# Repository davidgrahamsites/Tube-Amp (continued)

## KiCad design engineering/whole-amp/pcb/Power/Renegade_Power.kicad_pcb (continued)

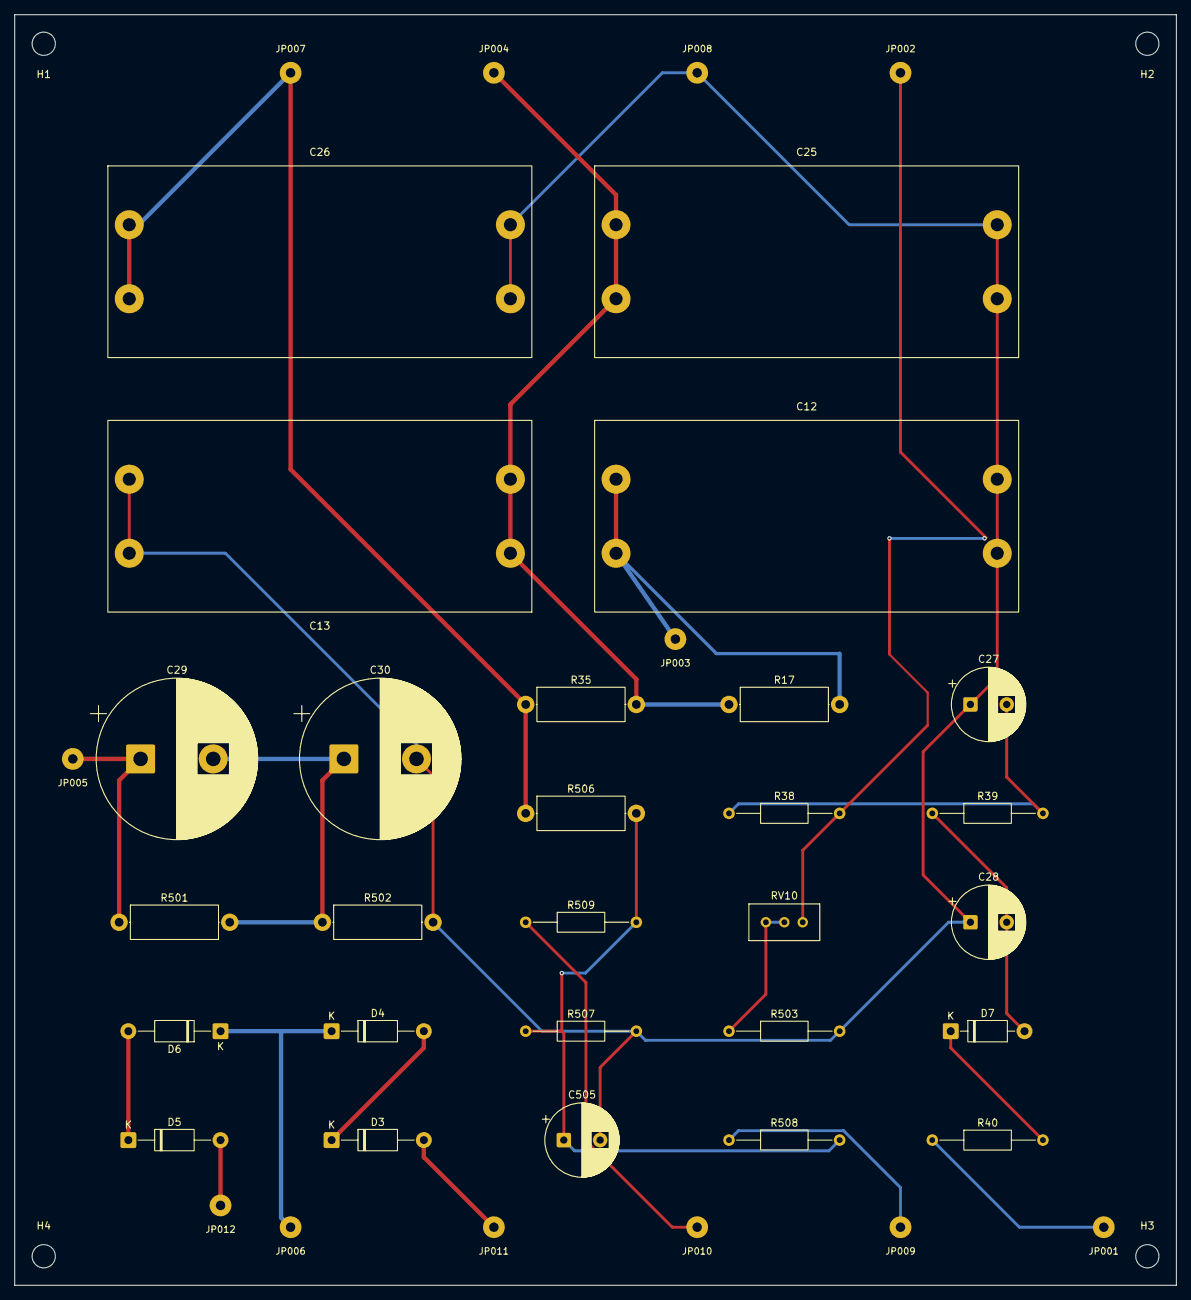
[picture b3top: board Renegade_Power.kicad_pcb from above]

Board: 2 copper layers, 160.0 x 175.0 mm, 43 parts (0 on the bottom side), 20 nets.

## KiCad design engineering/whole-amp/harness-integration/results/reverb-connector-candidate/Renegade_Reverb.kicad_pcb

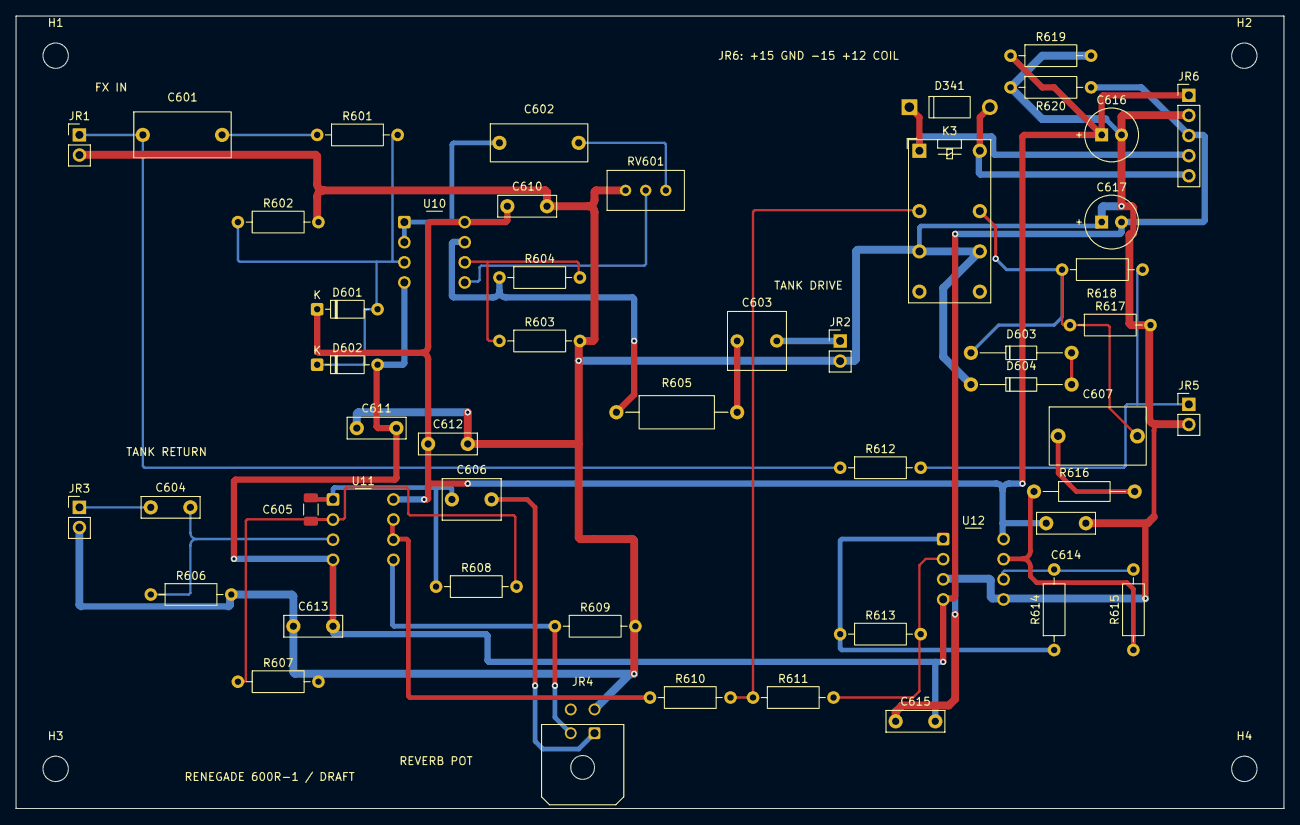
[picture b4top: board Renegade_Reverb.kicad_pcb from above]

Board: 2 copper layers, 160.0 x 100.0 mm, 55 parts (0 on the bottom side), 31 nets.

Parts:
C601: 100n; KYET_KP104J2J1006
C602: 22n; KYET_KP223J2J1001
C603: 2.2u; C_Rect_L7.2mm_W7.2mm_P5.00mm
C604, C610, C611, C612, C613, C614, C615: 100n; KNSCHA_MEB104J63V82CB0236
C605: 330p; C_1206_3216Metric
C606: 1u; KNSCHA_MEB105J63V82CB0235
C607: 1u; KNSCHA_MPP105J2W10KN22605
C616, C617: 47u; Panasonic_EEUFR1H470
D341: 1N4007 flyback; Onsemi_1N4007RLG_P10.16
D601, D602: 1N4148; D_DO-35_SOD27_P7.62mm_Horizontal
D603, D604: BZX55C27; Vishay_BZX55_DO35_P12.7
H1, H2, H3, H4: MountingHole_3.2mm_M3
JR1: JR1 harness; PinHeader_1x02_P2.54mm_Vertical
JR2: JR2 harness; PinHeader_1x02_P2.54mm_Vertical
JR3: JR3 harness; PinHeader_1x02_P2.54mm_Vertical
JR4: 430450402; Molex_Micro-Fit_3.0_43045-0400_2x02_P3.00mm_Horizontal
JR5: JR5 harness; PinHeader_1x02_P2.54mm_Vertical
JR6: JR6 harness; PinHeader_1x05_P2.54mm_Vertical
K3: G5V-2-H1 DC12; Omron_G5V_2_H1_PTH1mm
R601, R609, R617, R618: 1M; Yageo_MFR50S_MF0207_P10.16
R602, R608, R611, R612, R613, R614, R615: 100k; Yageo_MFR50S_MF0207_P10.16
R603, R604, R610, R619, R620: 10k; Yageo_MFR50S_MF0207_P10.16
R605: 220; Yageo_FMP200_P15.24_Drill0.9
R606: 220k; Yageo_MFR50S_MF0207_P10.16
R607: 1k; Yageo_MFR50S_MF0207_P10.16
R616: 100; Vishay_PR01_P12.7
RV601: 100k SEND trim; Bourns_3296W_TopAdjust_P2.54
U10, U11, U12: OPA2134PA; TE_1-2199298-2_DIP8_Socket

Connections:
+12V: D341.1, JR6.4, K3.1
+15V: C610.1, C612.1, C614.1, C616.1, D601.1, JR6.1, R619.1, U10.8, U11.8, U12.8
-15V: C611.2, C613.2, C615.2, C617.2, D602.2, JR6.3, R620.2, U10.4, U11.4, U12.4
COIL_REV: D341.2, JR6.5, K3.16
DRIVER: R604.1, R605.1, U10.7
DRIVE_CAP: C603.1, R605.2
DRV_FB: R603.1, R604.2, U10.6
FX_RETURN: C601.1, JR1.1, R612.1
GND: C610.2, C611.1, C612.2, C613.1, C614.2, C615.1, C616.2, C617.1, D604.1, JR1.2, JR2.2, JR3.2, JR4.3, JR5.2, JR6.2, K3.6, K3.11, R602.2, R603.2, R606.2, R607.2, R609.2, R617.2, R619.2, R620.1, RV601.3, U12.3, U12.5
IN_AC: C601.2, R601.1
MIX_OUT: JR5.1, R612.2, R618.2
OUT_AC: C607.1, R616.2
OUT_BUF: R615.1, R616.1, U12.7
OUT_FB: R614.2, R615.2, U12.6
REC_FB: C605.2, R607.1, R608.2, U11.2
REC_IN: C604.2, R606.1, U11.3
REC_OUT: C605.1, C606.1, R608.1, U11.1
SEND_BUF: C602.1, U10.1, U10.2
SEND_IN: D601.2, D602.1, R601.2, R602.1, U10.3
SEND_TOP: C602.2, RV601.1
SEND_W: RV601.2, U10.5
SUM: R611.2, R613.2, U12.2
SUM_INV: R613.1, R614.1, U12.1
TANK_IN: C603.2, JR2.1
TANK_OUT: C604.1, JR3.1
WET_AC: C607.2, D603.1, K3.13, R617.1, R618.1
WET_BUF: R610.1, U11.6, U11.7
WET_MUTE: K3.4, R610.2, R611.1
WET_TOP: C606.2, JR4.1
WET_W: JR4.2, R609.1, U11.5
WET_Z_JOIN: D603.2, D604.2
